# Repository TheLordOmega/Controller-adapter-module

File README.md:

# Dongle Host Module for HackXpansion console

A USB-host bridge module that lets a full sized controller to be be read by the Hackxpansion console.

Key features:
* Raspberry Pi Pico as the USB host controller
* Boost-converter-fed VBUS so the Pico can power the dongle
* UART link to the console over the J1 connector
## PCB

## Schematic

## 3D Case

## Bill of Materials (excluding console)
Also found in [bom.csv](./bom.csv).

| Item                                        | Price per unit                   | Nr of units | Total price            | Link                                                    |
| ------------------------------------------- | -------------------------------- | ----------- | ---------------------- | ------------------------------------------------------- |
| Raspberry Pi Pico                           | $4.00                            | 1           | $4.00                  | https://www.raspberrypi.com/products/raspberry-pi-pico/ |
| MT3608 boost converter breakout             | ~$1-4 (pack pricing varies)      | 1           | ~$1-4                  | -                                                       |
| 2x20 2.54mm female pin socket (Pico mount)  |  -                               | 1           | -                      | -                                                       |
| 2x7 2.54mm pin header (J1)                  | ~$0.20-0.39                      | 1           | ~$0.20-0.39            | https://www.aliexpress.com/item/4000186187780.html      |
| 1x04 2.54mm pin header (boost converter)    | ~$0.10                           | 1           | ~$0.10                 | -                                                       |
| 1x02 2.54mm pin header + jumper (power cut) | ~$0.10                           | 1           | ~$0.10                 | -                                                       |
| MD0/MD1 ID resistors, 0603                  |-                                 | 2           | -                      | -                                                       |
| 10uF electrolytic + 100nF ceramic cap       | -                                | 1 each      | -                      | -                                                       |
| Micro-USB-to-USB-A OTG adapter cable        |  -                               | 1           | -                      | -                                                       |
| PCB fab                                     |   -                              | 1           | -                      | https://jlcpcb.com/                                     |
| **Total**                                   |                                  |             | ~$10 without controller |                                                         |

## Credits
* USB host HID parsing (DS4 report handling): [TinyUSB](https://github.com/hathach/tinyusb),
  `examples/host/hid_controller/src/hid_app.c`, by hathach and contributors
* Console-side UART driver pattern:   [`wardriving-driver`](https://docs.rs/crate/wardriving-driver) crate's UART bus usage
* Driver : [`xpanse_api`](https://docs.rs/xpanse-api)
* Raspberry Pi Pico hardware: [Raspberry Pi](https://www.raspberrypi.com/products/raspberry-pi-pico/)
* Thanks to Hack Club and the HackXpansion team for the console platform this module plugs into: https://github.com/hackclub/hackxpansion
* Thanks to the OpenSplitDeck project for the dongle this module is built to read as an example

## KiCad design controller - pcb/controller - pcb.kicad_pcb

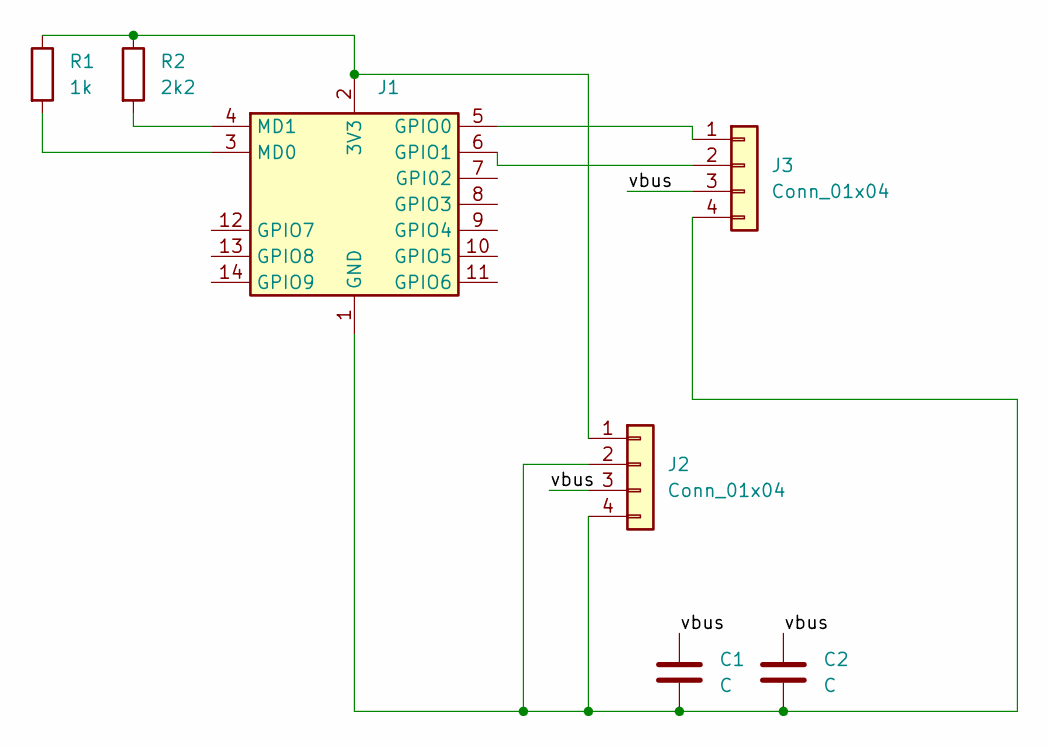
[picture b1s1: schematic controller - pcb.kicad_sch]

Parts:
C1, C2: C; C_0603_1608Metric
J1: Male_Module
J2, J3: Conn_01x04; PinHeader_1x04_P2.54mm_Vertical
R1: 1k; R_0603_1608Metric
R2: 2k2; R_0603_1608Metric

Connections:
/vbus: C1.1, C2.1, J2.3, J3.3
unnamed: J1.2 (3V3), J2.1, R1.1, R2.1
unnamed: C1.2, C2.2, J1.1 (GND), J2.2, J2.4, J3.4
unnamed: J1.5 (GPIO0), J3.1
unnamed: J1.6 (GPIO1), J3.2
unnamed: J1.3 (MD0), R1.2
unnamed: J1.4 (MD1), R2.2

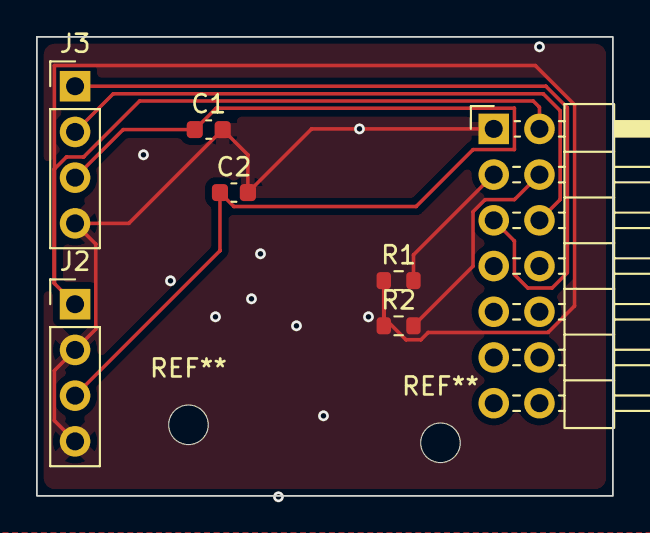
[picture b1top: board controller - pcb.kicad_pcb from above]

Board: 2 copper layers, 32.0 x 25.5 mm, 7 parts (0 on the bottom side), 7 nets.
